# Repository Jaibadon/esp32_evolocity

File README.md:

# Evolocity Monotoring board using ESP32-C3 Chip with external flash capabilitiy
RPM, Voltage, Current and temperature sensing

AH1390 Hall Effect(Rpm)
ACS711 Current monitor

SPX3819 Low dropout reg

Designed in Kicad 7.0

Low pass Pi matching nework simulated using 4Nec2.

Quality factor = 2

Pi Matching results:

Xp1 = ~2pF

Xp2= ~2pF

Xs = 2.2nH

Due to Xp values being in the <~3pF range they are negligible and will be part of the parasitic capacitance.

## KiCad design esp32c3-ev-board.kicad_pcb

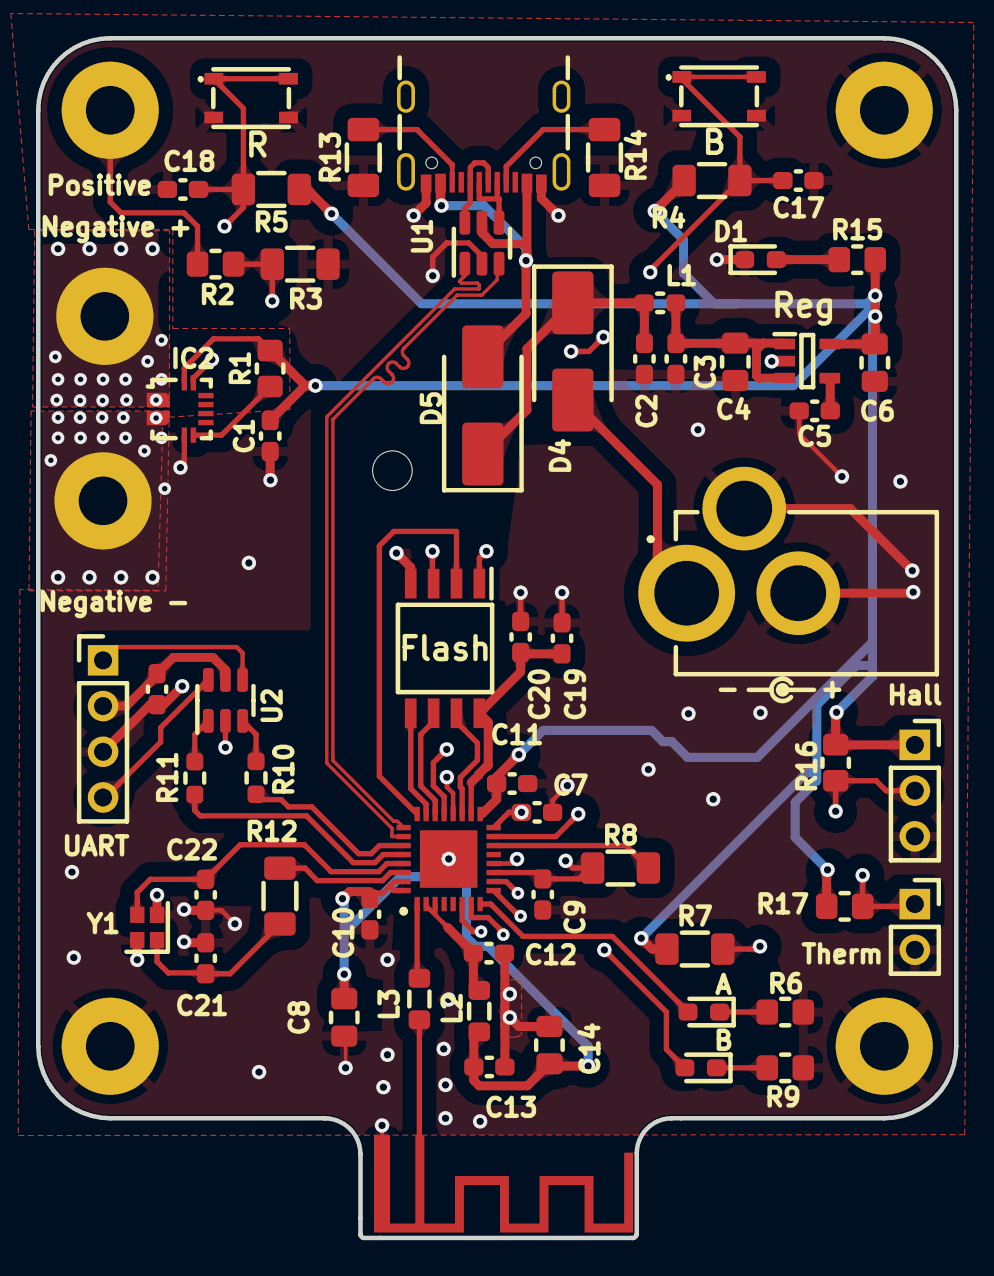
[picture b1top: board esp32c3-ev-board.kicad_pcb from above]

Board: 4 copper layers, 51.0 x 66.7 mm, 68 parts (0 on the bottom side), 48 nets.

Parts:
A: LED A; LED_0603_1608Metric_Pad1.05x0.95mm_HandSolder
ANT1: antenna
B: LED B; LED_0603_1608Metric_Pad1.05x0.95mm_HandSolder
B#2: SW_DPST_x2; SKRPADE010
C1: 0.1 uF; C_0603_1608Metric_Pad1.08x0.95mm_HandSolder
C2, C3, C5, C9, C10, C11, C12, C13, C17, C18, C19, C23: 100n; C_0603_1608Metric_Pad1.08x0.95mm_HandSolder
C4, C6, C8, C14: 10u; C_0805_2012Metric_Pad1.18x1.45mm_HandSolder
C7: 100nF; C_0603_1608Metric_Pad1.08x0.95mm_HandSolder
C20: 10u; C_0603_1608Metric_Pad1.08x0.95mm_HandSolder
C21, C22: 10p; C_0603_1608Metric_Pad1.08x0.95mm_HandSolder
D1: LED A; LED_0603_1608Metric_Pad1.05x0.95mm_HandSolder
D4, D5: D; D_SMB_Handsoldering
Flash: W25Q128JVSIQ; SOIC127P790X216-8N
H1, H3, H4: MountingHole_Pad; MountingHole_2.7mm_M2.5_Pad
H7: MountingHole_Pad; MountingHole_2.2mm_M2
Hall: Screw_Terminal_01x03; PinSocket_1x03_P2.54mm_Vertical
IC2: ACS711EEXTK-31AB-T; Allegro_QFN-12-10-1EP_3x3mm_P0.5mm
IC3: ESP32-C3FH4; QFN50P500X500X90-33N-D
J2: DC Connecter; KLDX0202A
J5: USB_C_Receptacle_USB2.0; USB_C_Receptacle_GCT_USB4105-xx-A_16P_TopMnt_Horizontal
L1: 2n2; L_0603_1608Metric_Pad1.05x0.95mm_HandSolder
L2, L3: 2n2; L_0805_2012Metric_Pad1.05x1.20mm_HandSolder
Negative +: MountingHole_Pad; MountingHole_2.7mm_M2.5_Pad
Negative -: MountingHole_Pad; MountingHole_2.7mm_M2.5_Pad
Positive: MountingHole_Pad; MountingHole_2.7mm_M2.5_Pad
R: SW_DPST_x2; SKRPADE010
R1: 1kR; R_0805_2012Metric_Pad1.20x1.40mm_HandSolder
R2: 100k; R_0805_2012Metric_Pad1.20x1.40mm_HandSolder
R3: 5.1k; R_1206_3216Metric_Pad1.30x1.75mm_HandSolder
R4, R5, R7, R8, R13, R14: 5k1; R_1206_3216Metric_Pad1.30x1.75mm_HandSolder
R6, R9, R15, R16, R17: 1k; R_0805_2012Metric_Pad1.20x1.40mm_HandSolder
R10, R11: 470R; R_0603_1608Metric_Pad0.98x0.95mm_HandSolder
R12: 22R; R_1206_3216Metric_Pad1.30x1.75mm_HandSolder
Reg: SPX3819M5-L-3-3; SOT95P280X145-5N
Therm: Battery Neg(Series); PinSocket_1x02_P2.54mm_Vertical
U1, U2: USBLC6-2SC6; SOT-23-6
UART: Conn_01x04_Pin; PinHeader_1x04_P2.54mm_Vertical
Y1: 40MHZ; Crystal_SMD_2016-4Pin_2.0x1.6mm

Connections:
3V3 RF: C12.1, IC3.2 (VDD3P3_1), IC3.3 (VDD3P3_2), L2.1
5vUSB: D5.2 (A), J5.A4 (VBUS), J5.A9 (VBUS), J5.B4 (VBUS), J5.B9 (VBUS), U1.5 (VBUS)
+3.3V: C1.2, C6.1, C8.1, C9.1, C10.1, C11.1, C13.1, C14.1, Hall.1, IC2.12 (VCC), IC3.11 (VDD3P3_RTC), IC3.17 (VDD3P3_CPU), IC3.31 (VDDA_1), IC3.32 (VDDA_2), L2.2, R1.2, R4.1, R5.1, R7.1, R8.1, R15.2, R16.1, R17.2, Reg.5 (VOUT)
CHIPEN: C18.1, IC3.7 (CHIP_EN), R.1 (A), R.2 (B), R5.2
CurMeas: B#2.1 (A), B#2.2 (B), C17.1, IC2.11 (VIOUT), IC3.15 (GPIO9), R4.2
LED A: A.2 (A), IC3.8 (GPIO3)
LED B: B.2 (A), IC3.12 (MTCK)
unnamed: ANT1.1, L3.1
unnamed: C21.1, R12.2, Y1.1
unnamed: D1.2 (A), R15.1
unnamed: A.1 (K), R6.2
unnamed: D4.2 (A), J2.1
unnamed: B.1 (K), R9.2
unnamed: C5.1, Reg.4 (ADJ/BYP)
unnamed: C3.1, C4.1, L1.2, Reg.1 (VIN), Reg.3 (EN)
unnamed: IC2.6 (~FAULT), R1.1
unnamed: IC3.6 (GPIO2), R7.2
unnamed: IC3.14 (GPIO8), R8.2
unnamed: IC3.1 (LNA_IN), L3.2
unnamed: Hall.2, IC3.10 (MTDI), R16.2
unnamed: IC3.9 (MTMS), R17.1, Therm.1
unnamed: Flash.6 (CLK), IC3.22 (SPICLK)
unnamed: Flash.1 (/CS), IC3.21 (SPICS0)
unnamed: Flash.5 (DI_(IO0)), IC3.23 (SPID)
unnamed: Flash.7 (HD(IO3)), IC3.19 (SPIHD)
unnamed: Flash.2 (DO_(IO1)), IC3.24 (SPIQ)
unnamed: Flash.3 (/WP_(IO2)), IC3.20 (SPIWP)
unnamed: IC3.27 (U0RXD), R10.2
unnamed: IC3.28 (U0TXD), R11.2
unnamed: C19.1, C20.1, Flash.8 (VCC), IC3.18 (VDD_SPI)
unnamed: C22.1, IC3.29 (XTAL_N), Y1.3
unnamed: IC3.30 (XTAL_P), R12.1
unnamed: U2.4 (I/O2), UART.1
unnamed: U2.6 (I/O1), UART.4
unnamed: J5.A5 (CC1), R14.1
unnamed: J5.B5 (CC2), R13.2
unnamed: J5.A6 (D+), J5.B6 (D+), U1.6 (I/O1)
unnamed: J5.A7 (D-), J5.B7 (D-), U1.4 (I/O2)
Reg Neg: ANT1.2, B#2.3 (B), B#2.4 (B), C1.1, C2.2, C3.2, C4.2, C5.2, C6.2, C7.2, C8.2, C9.2, C10.2, C11.2, C12.2, C13.2, C14.2, C17.2, C18.2, C19.2, C20.2, C21.2, C22.2, C23.2, D1.1 (K), Flash.4 (GND), H1.1, H3.1, H4.1, Hall.3, IC2.4 (IP-), IC2.5 (GND), IC3.33 (GND), J2.2, J2.3, J5.A1 (GND), J5.A12, J5.B1, J5.B12, Negative -.1, R.3 (B), R.4 (B), R3.2, R6.1, R9.1, R13.1, R14.2, Reg.2 (GND), Therm.2, U1.2 (GND), U2.2 (GND), UART.3, Y1.2, Y1.4
Reg Pos: C2.1, D4.1 (K), D5.1 (K), L1.1
UARTRX: R10.1, U2.3 (I/O2)
UARTTX: R11.1, U2.1 (I/O1)
USBD+: IC3.26 (GPIO19), U1.1 (I/O1)
USBD-: IC3.25 (GPIO18), U1.3 (I/O2)
UnregNeg(furthest from bat term): IC2.1 (IP+), Negative +.1
UnregPos: Positive.1, R2.1
VBUS: C23.1, U2.5 (VBUS), UART.2
VoltMeas: C7.1, IC3.16 (GPIO10), R2.2, R3.1

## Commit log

2023-07-25 Init commit
2023-07-25 Crystal added
2023-07-25 rando resistor test
2023-07-26 Flash Memory Added
2023-07-26 Cleaning up Schematic
2023-07-26 Added Chip Enable Switch
2023-07-26 Tidy values and usb/esd prot
2023-07-27 working on voltage and voltage mux
2023-07-27 Added Power supply diodes
2023-07-27 box test
2023-07-27 removing backup folder
2023-07-27 added LEDs
2023-07-28 rearranging schematic
2023-08-01 change voltreg
2023-08-01 volt reg work
2023-08-02 Added Footprints and transfered to PCB
2023-08-02 Arranged some of the components for less crosses in the pcb
2023-08-04 Did some pcb changes
2023-08-09 Changed footprints
2023-08-09 Assigned new switch and DC connecter footprints
2023-08-09 placement and routing ideas
2023-08-09 shape and placement nearly finished, doing perephirals next
2023-08-10 almost completed board layout
2023-08-10 starting outline REMEMBER TO ORDER 100k resistor size 0805
2023-08-11 finished outline
2023-08-13 Almost finished
2023-08-15 finishing touches
2023-08-15 PCBWAY VER || SWITCHING TO JLC
2023-08-15 ordered board
2023-08-16 3d models
